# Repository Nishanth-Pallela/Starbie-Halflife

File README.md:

# Starbie

Starbie is a tiny, digital pet. It is basically a merge of a Tamagotchi and a Starboy!
Made for Half Life from Hackclub (Check it out!!!)

## How it works

It uses an environmental sensor and an mpu to process motion and temperature. 
It can display a cute animation on a small oled screen. 
You can also use the rotary encoder to change animations!
AND ITS BATTERY POWERED!!!

### Reference

This was based on the starter project from the half life event. This is the [link](https://github.com/SharKingStudios/Starbie) to the repository of the original.

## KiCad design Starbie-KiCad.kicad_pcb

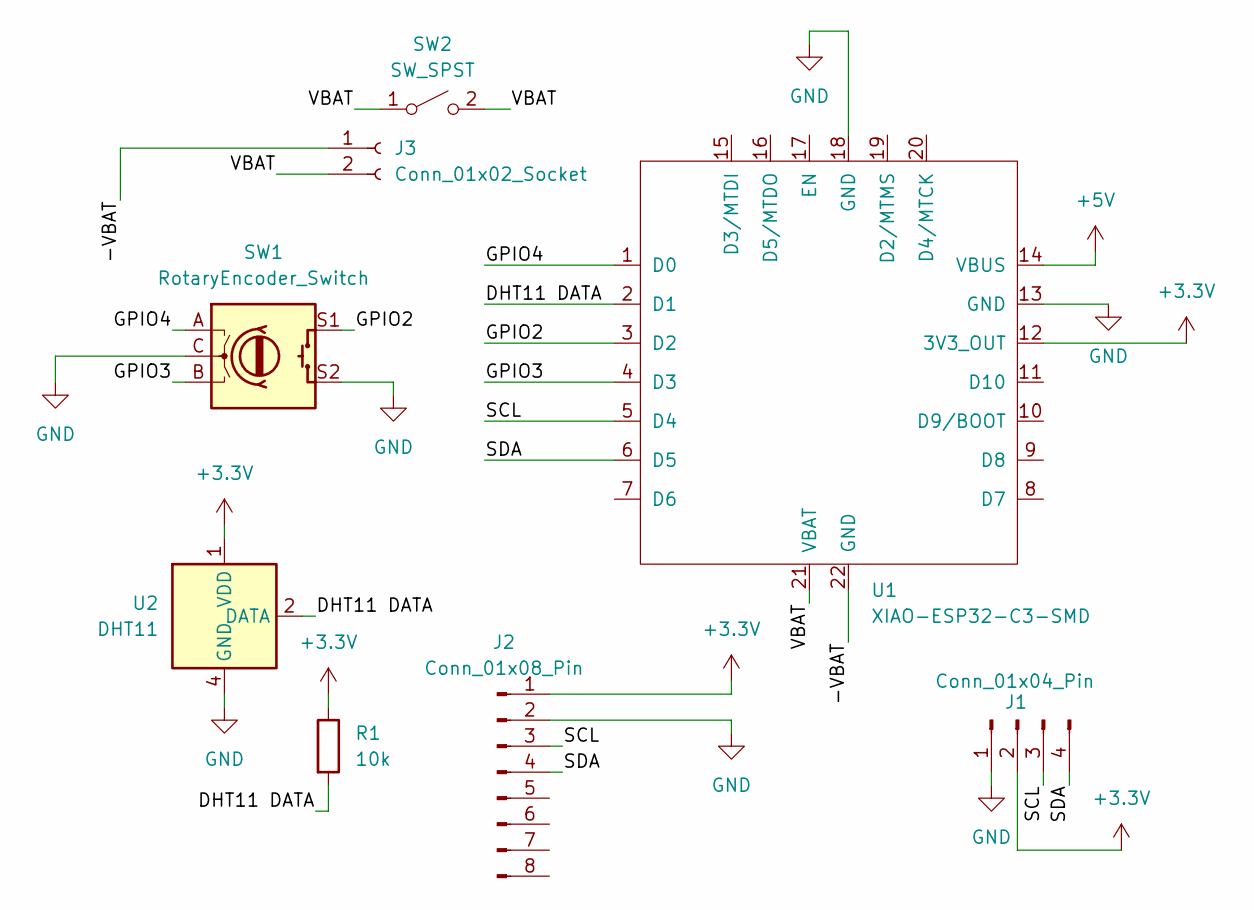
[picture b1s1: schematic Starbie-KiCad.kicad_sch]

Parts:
J1: Conn_01x04_Pin; Display_128x64_096_I2C
J2: Conn_01x08_Pin; PinHeader_1x08_P2.54mm_Vertical
J3: Conn_01x02_Socket; JST_PH_B2B-PH-K_1x02_P2.00mm_Vertical
R1: 10k; R_Axial_DIN0204_L3.6mm_D1.6mm_P7.62mm_Horizontal
SW1: RotaryEncoder_Switch; RotaryEncoder_Alps_EC11E-Switch_Vertical_H20mm
SW2: SW_SPST; SW_DIP_SPSTx01_Piano_10.8x4.1mm_W7.62mm_P2.54mm
U1: XIAO-ESP32-C3-SMD
U2: DHT11; Aosong_DHT11_5.5x12.0_P2.54mm

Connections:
+3.3V: J1.2, J2.1, R1.1, U1.12 (3V3_OUT), U2.1 (VDD)
+5V: U1.14 (VBUS)
/-VBAT: J3.1, U1.22 (GND)
/DHT11 DATA: R1.2, U1.2 (D1), U2.2 (DATA)
/GPIO2: SW1.S1, U1.3 (D2)
/GPIO3: SW1.B, U1.4 (D3)
/GPIO4: SW1.A, U1.1 (D0)
/SCL: J1.3, J2.3, U1.5 (D4)
/SDA: J1.4, J2.4, U1.6 (D5)
/VBAT: J3.2, SW2.1 (A), SW2.2 (B), U1.21 (VBAT)
GND: J1.1, J2.2, SW1.C, SW1.S2, U1.13 (GND), U1.18 (GND), U2.4 (GND)

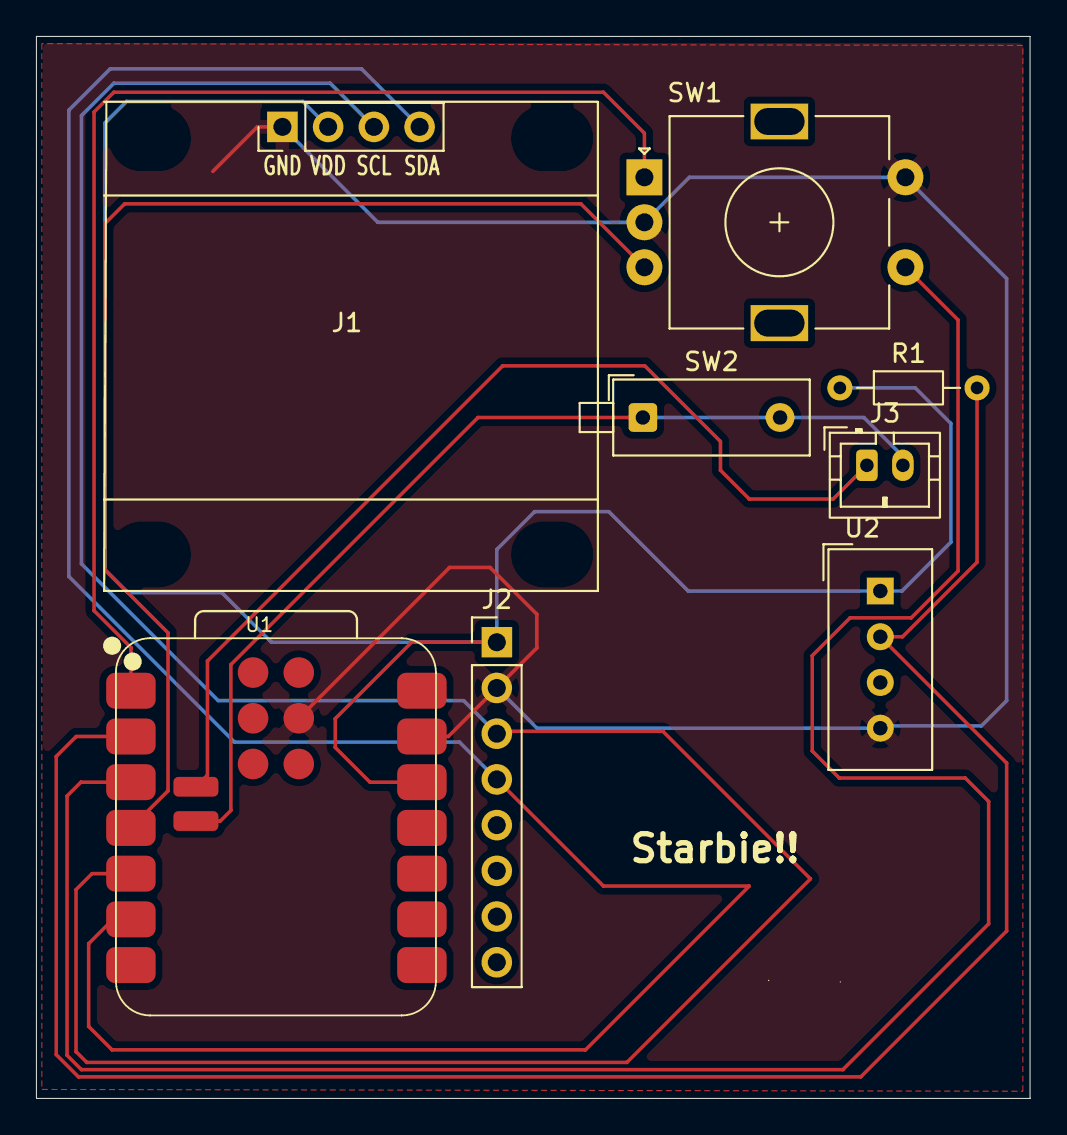
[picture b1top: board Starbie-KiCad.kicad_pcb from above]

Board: 2 copper layers, 55.2 x 59.0 mm, 9 parts (0 on the bottom side), 10 nets.

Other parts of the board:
Starbie!!: LOGO
